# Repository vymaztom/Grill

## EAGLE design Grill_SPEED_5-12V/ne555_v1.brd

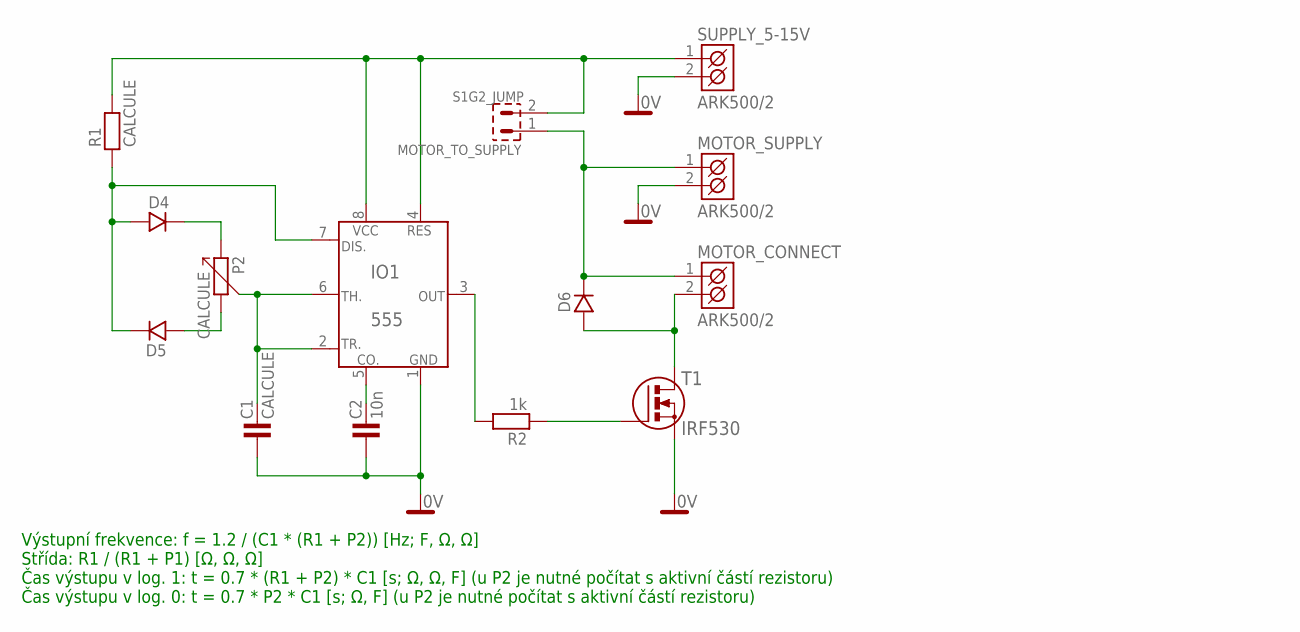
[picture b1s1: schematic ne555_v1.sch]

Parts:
C1: CALCULE; C-7,5
C2: 10n; C-7,5
D4, D5, D6: D_7,5; DO35
IO1: 555; DIL8
MOTOR_CONNECT: ARK500/2
MOTOR_SUPPLY: ARK500/2
MOTOR_TO_SUPPLY: S1G2_JUMP; S1G2_JUM
P2: CALCULE; PC16ML
R1: CALCULE; R-7,5
R2: 1k; R-7,5
SUPPLY_5-15V: ARK500/2
T1: IRF530; TO-220S

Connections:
0V: C1.1, C2.1, IO1.1 (GND), MOTOR_SUPPLY.2 (K2), SUPPLY_5-15V.2 (K2), T1.3 (S)
unnamed: D5.A, P2.2
unnamed: D4.K, P2.1
unnamed: D6.K, MOTOR_CONNECT.1 (K1), MOTOR_SUPPLY.1 (K1), MOTOR_TO_SUPPLY.1
unnamed: D6.A, MOTOR_CONNECT.2 (K2), T1.2 (D)
unnamed: R2.1, T1.1 (G)
unnamed: IO1.3 (OUT), R2.2
unnamed: C2.2, IO1.5 (CO.)
unnamed: D4.A, D5.K, IO1.7 (DIS.), R1.1
unnamed: C1.2, IO1.2 (TR.), IO1.6 (TH.), P2.3
unnamed: IO1.4 (RES), IO1.8 (VCC), MOTOR_TO_SUPPLY.2, R1.2, SUPPLY_5-15V.1 (K1)

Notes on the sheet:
Výstupní frekvence: f = 1.2 / (C1 * (R1 + P2)) [Hz; F, Ω, Ω] Střída: R1 / (R1 + P1) [Ω, Ω, Ω] Čas výstupu v log. 1: t = 0.7 * (R1 + P2) * C1 [s; Ω, Ω, F] (u P2 je nutné počítat s aktivní částí rezistoru) Čas výstupu v log. 0: t = 0.7 * P2 * C1 [s; Ω, F] (u P2 je nutné počítat s aktivní částí rezist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

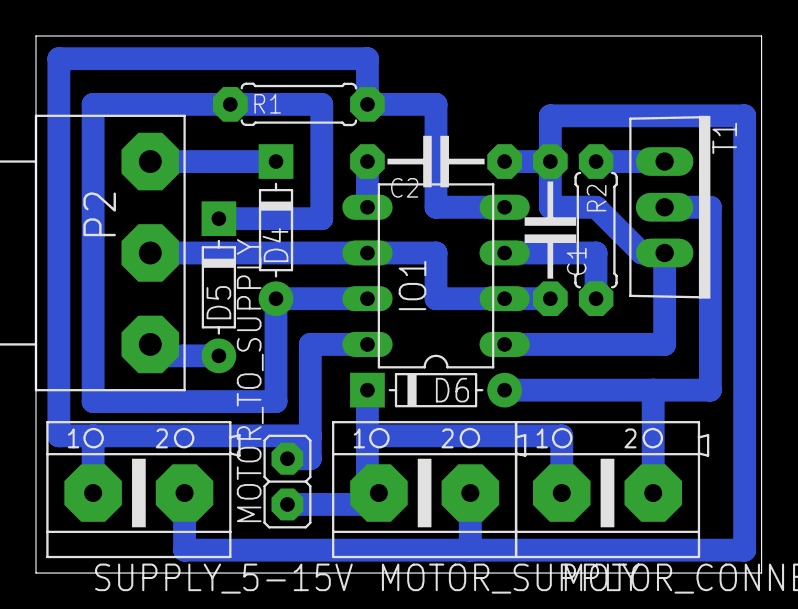
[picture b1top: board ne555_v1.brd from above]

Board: 2 copper layers, 40.3 x 29.8 mm, 14 parts (0 on the bottom side), 11 nets.

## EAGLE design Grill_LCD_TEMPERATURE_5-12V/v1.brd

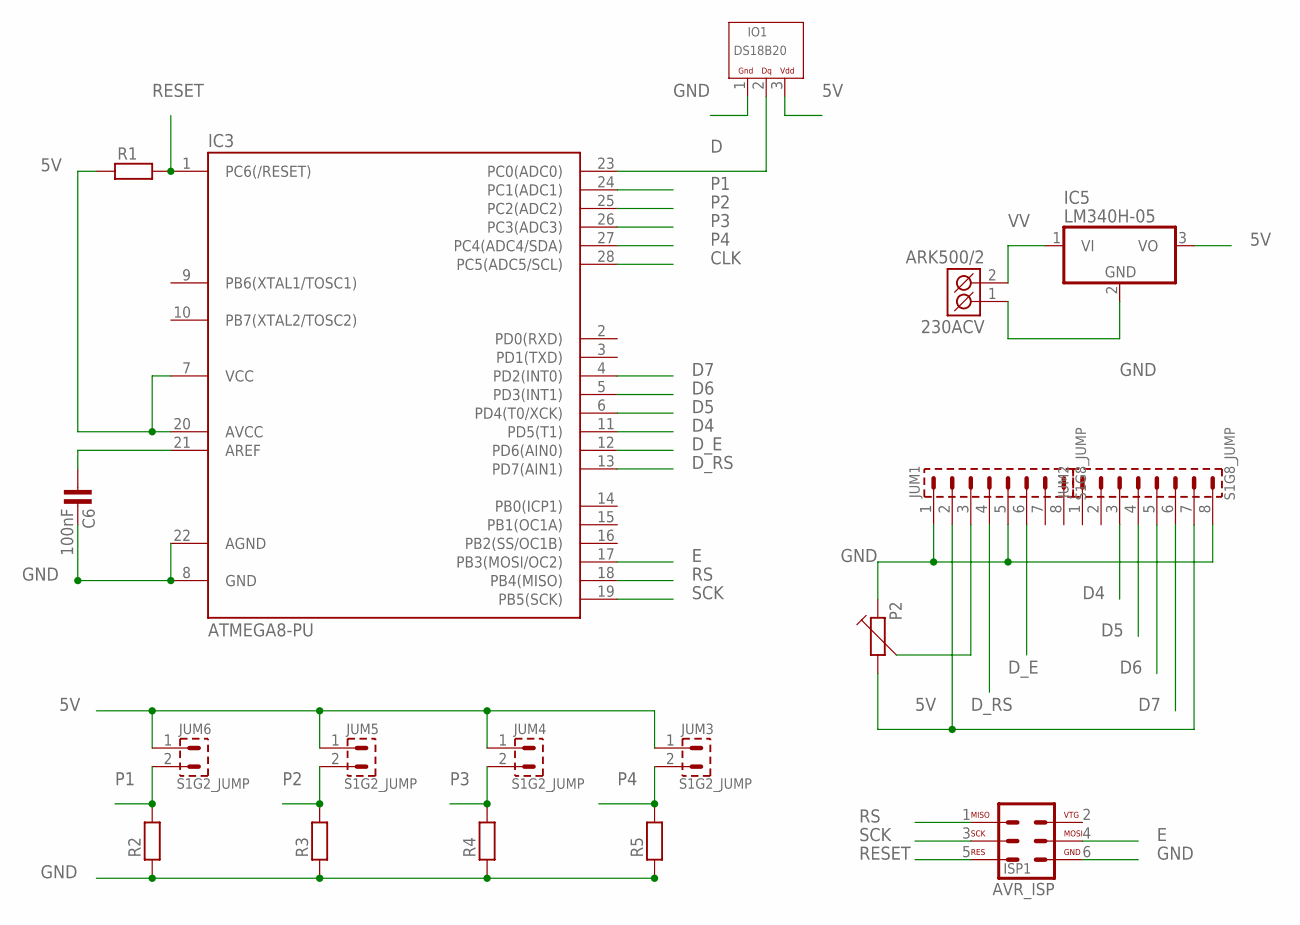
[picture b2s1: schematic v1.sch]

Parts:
230ACV: ARK500/2
C6: 100nF; C-2,5
IC3: ATMEGA8-PU; DIL28-3
IC5: LM340H-05; TO220H
IO1: DS18B20; TO-92
ISP1: AVR_ISP; MLW06G
JUM1, JUM2: S1G8_JUMP; S1G8_JUM
JUM3, JUM4, JUM5, JUM6: S1G2_JUMP; S1G2_JUM
P2: TRIMRPT6V; PT6V
R1, R2, R3, R4, R5: R_7,5; R-7,5

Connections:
5V: IC3.7 (VCC), IC3.20 (AVCC), IC5.3 (VO), IO1.3 (+VCC), JUM1.2, JUM2.7, JUM3.1, JUM4.1, JUM5.1, JUM6.1, P2.2, R1.1
CLK: IC3.28 (PC5(ADC5/SCL))
D: IC3.23 (PC0(ADC0)), IO1.2 (1WIRE)
D4: IC3.11 (PD5(T1)), JUM2.3
D5: IC3.6 (PD4(T0/XCK)), JUM2.4
D6: IC3.5 (PD3(INT1)), JUM2.5
D7: IC3.4 (PD2(INT0)), JUM2.6
D_E: IC3.12 (PD6(AIN0)), JUM1.6
D_RS: IC3.13 (PD7(AIN1)), JUM1.4
E: IC3.17 (PB3(MOSI/OC2)), ISP1.4
GND: 230ACV.1 (K1), C6.2, IC3.8 (GND), IC3.22 (AGND), IC5.2 (GND), IO1.1 (GND), ISP1.6, JUM1.1, JUM1.5, JUM2.8, P2.1, R2.1, R3.1, R4.1, R5.1
unnamed: C6.1, IC3.21 (AREF)
unnamed: JUM1.3, P2.3
P1: IC3.24 (PC1(ADC1)), JUM6.2, R2.2
P2: IC3.25 (PC2(ADC2)), JUM5.2, R3.2
P3: IC3.26 (PC3(ADC3)), JUM4.2, R4.2
P4: IC3.27 (PC4(ADC4/SDA)), JUM3.2, R5.2
RESET: IC3.1 (PC6(/RESET)), ISP1.5, R1.2
RS: IC3.18 (PB4(MISO)), ISP1.1
SCK: IC3.19 (PB5(SCK)), ISP1.3
VV: 230ACV.2 (K2), IC5.1 (VI)

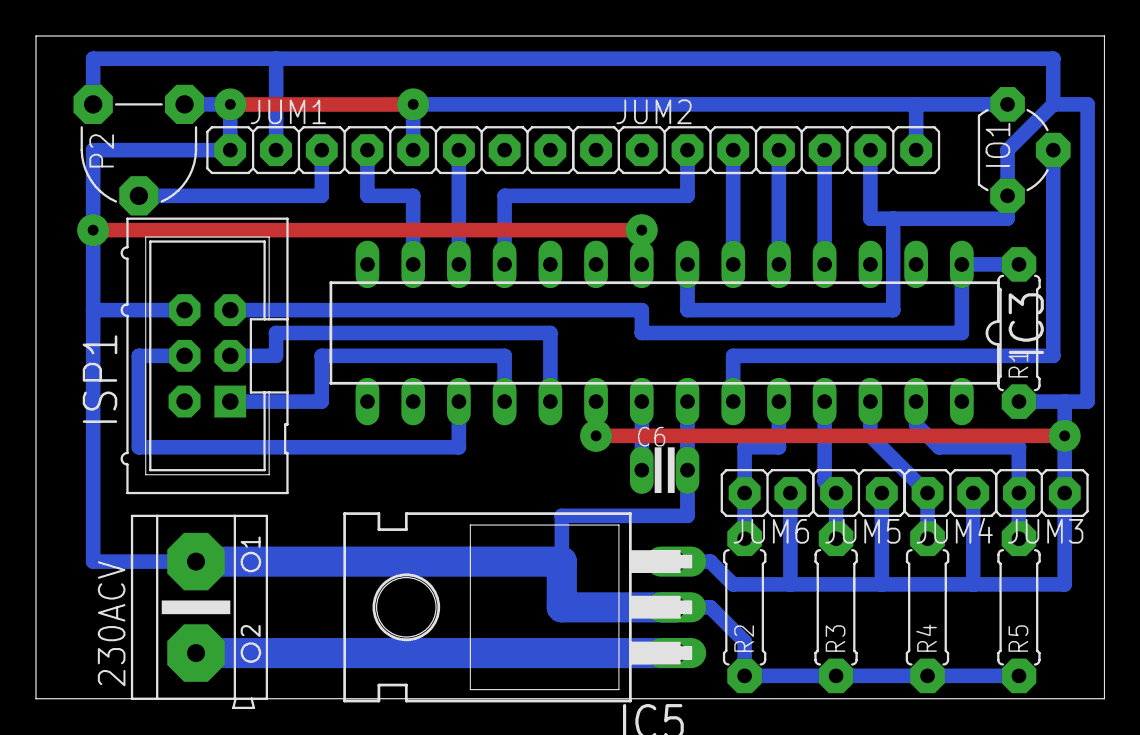
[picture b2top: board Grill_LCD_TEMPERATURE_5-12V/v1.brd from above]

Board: 2 copper layers, 59.4 x 36.8 mm, 18 parts (0 on the bottom side), 20 nets.

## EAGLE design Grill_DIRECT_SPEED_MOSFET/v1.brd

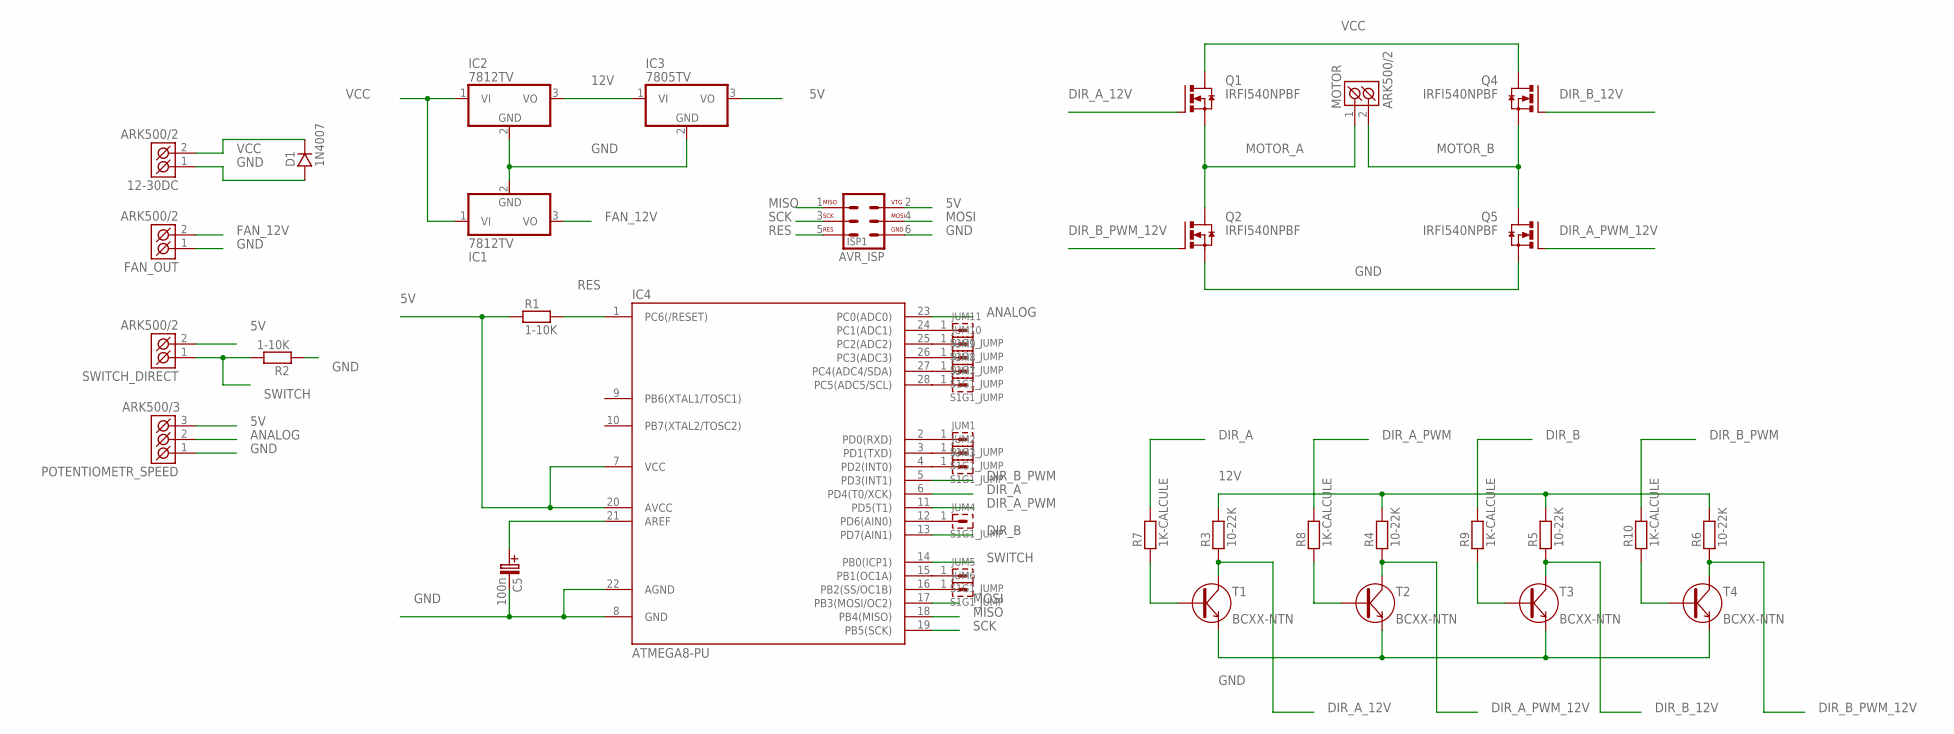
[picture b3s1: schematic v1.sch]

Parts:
12-30DC: ARK500/2
C5: 100n; C-EL_2,5
D1: 1N4007; DO41
FAN_OUT: ARK500/2
IC1, IC2: 7812TV; TO220V
IC3: 7805TV; TO220V
IC4: ATMEGA8-PU; DIL28-3
ISP1: AVR_ISP; MLW06G
JUM1, JUM2, JUM3, JUM4, JUM5, JUM6, JUM7, JUM8, JUM9, JUM10, JUM11: S1G1_JUMP; S1G1_JUM
MOTOR: ARK500/2
POTENTIOMETR_SPEED: ARK500/3
Q1, Q2, Q4, Q5: IRFI540NPBF; TO220BH
R1, R2: 1-10K; R-7,5
R3, R4, R5, R6: 10-22K; R-7,5
R7, R8, R9, R10: 1K-CALCULE; R-7,5
SWITCH_DIRECT: ARK500/2
T1, T2, T3, T4: BCXX-NTN; TO-92

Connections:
5V: IC3.3 (VO), IC4.7 (VCC), IC4.20 (AVCC), ISP1.2, POTENTIOMETR_SPEED.3 (K3), R1.1, SWITCH_DIRECT.2 (K2)
12V: IC2.3 (VO), IC3.1 (VI), R3.2, R4.2, R5.2, R6.2
ANALOG: IC4.23 (PC0(ADC0)), POTENTIOMETR_SPEED.2 (K2)
DIR_A: IC4.6 (PD4(T0/XCK)), R7.2
DIR_A_12V: Q1.G, R3.1, T1.1 (C)
DIR_A_PWM: IC4.11 (PD5(T1)), R8.2
DIR_A_PWM_12V: Q5.G, R4.1, T2.1 (C)
DIR_B: IC4.13 (PD7(AIN1)), R9.2
DIR_B_12V: Q4.G, R5.1, T3.1 (C)
DIR_B_PWM: IC4.5 (PD3(INT1)), R10.2
DIR_B_PWM_12V: Q2.G, R6.1, T4.1 (C)
FAN_12V: FAN_OUT.2 (K2), IC1.3 (VO)
GND: 12-30DC.1 (K1), C5.C- (C_EL-), D1.A, FAN_OUT.1 (K1), IC1.2 (GND), IC2.2 (GND), IC3.2 (GND), IC4.8 (GND), IC4.22 (AGND), ISP1.6, POTENTIOMETR_SPEED.1 (K1), Q2.S, Q5.S, R2.1, T1.3 (E), T2.3 (E), T3.3 (E), T4.3 (E)
MISO: IC4.18 (PB4(MISO)), ISP1.1
MOSI: IC4.17 (PB3(MOSI/OC2)), ISP1.4
MOTOR_A: MOTOR.1 (K1), Q1.S, Q2.D
MOTOR_B: MOTOR.2 (K2), Q4.S, Q5.D
unnamed: IC4.2 (PD0(RXD)), JUM1.1
unnamed: IC4.3 (PD1(TXD)), JUM2.1
unnamed: IC4.4 (PD2(INT0)), JUM3.1
unnamed: IC4.12 (PD6(AIN0)), JUM4.1
unnamed: C5.C+ (C_EL+), IC4.21 (AREF)
unnamed: R7.1, T1.2 (B)
unnamed: IC4.15 (PB1(OC1A)), JUM5.1
unnamed: IC4.16 (PB2(SS/OC1B)), JUM6.1
unnamed: R8.1, T2.2 (B)
unnamed: R9.1, T3.2 (B)
unnamed: R10.1, T4.2 (B)
unnamed: IC4.28 (PC5(ADC5/SCL)), JUM7.1
unnamed: IC4.27 (PC4(ADC4/SDA)), JUM8.1
unnamed: IC4.26 (PC3(ADC3)), JUM9.1
unnamed: IC4.25 (PC2(ADC2)), JUM10.1
unnamed: IC4.24 (PC1(ADC1)), JUM11.1
RES: IC4.1 (PC6(/RESET)), ISP1.5, R1.2
SCK: IC4.19 (PB5(SCK)), ISP1.3
SWITCH: IC4.14 (PB0(ICP1)), R2.2, SWITCH_DIRECT.1 (K1)
VCC: 12-30DC.2 (K2), D1.K, IC1.1 (VI), IC2.1 (VI), Q1.D, Q4.D

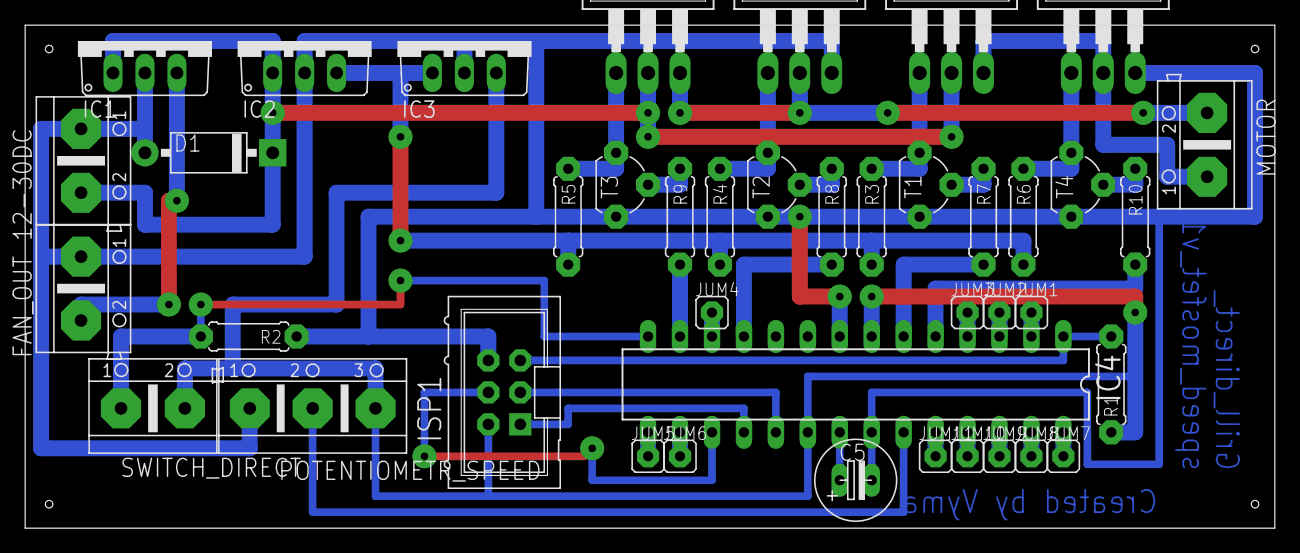
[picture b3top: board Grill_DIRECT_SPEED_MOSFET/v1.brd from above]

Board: 2 copper layers, 99.4 x 40.0 mm, 41 parts (0 on the bottom side), 37 nets.

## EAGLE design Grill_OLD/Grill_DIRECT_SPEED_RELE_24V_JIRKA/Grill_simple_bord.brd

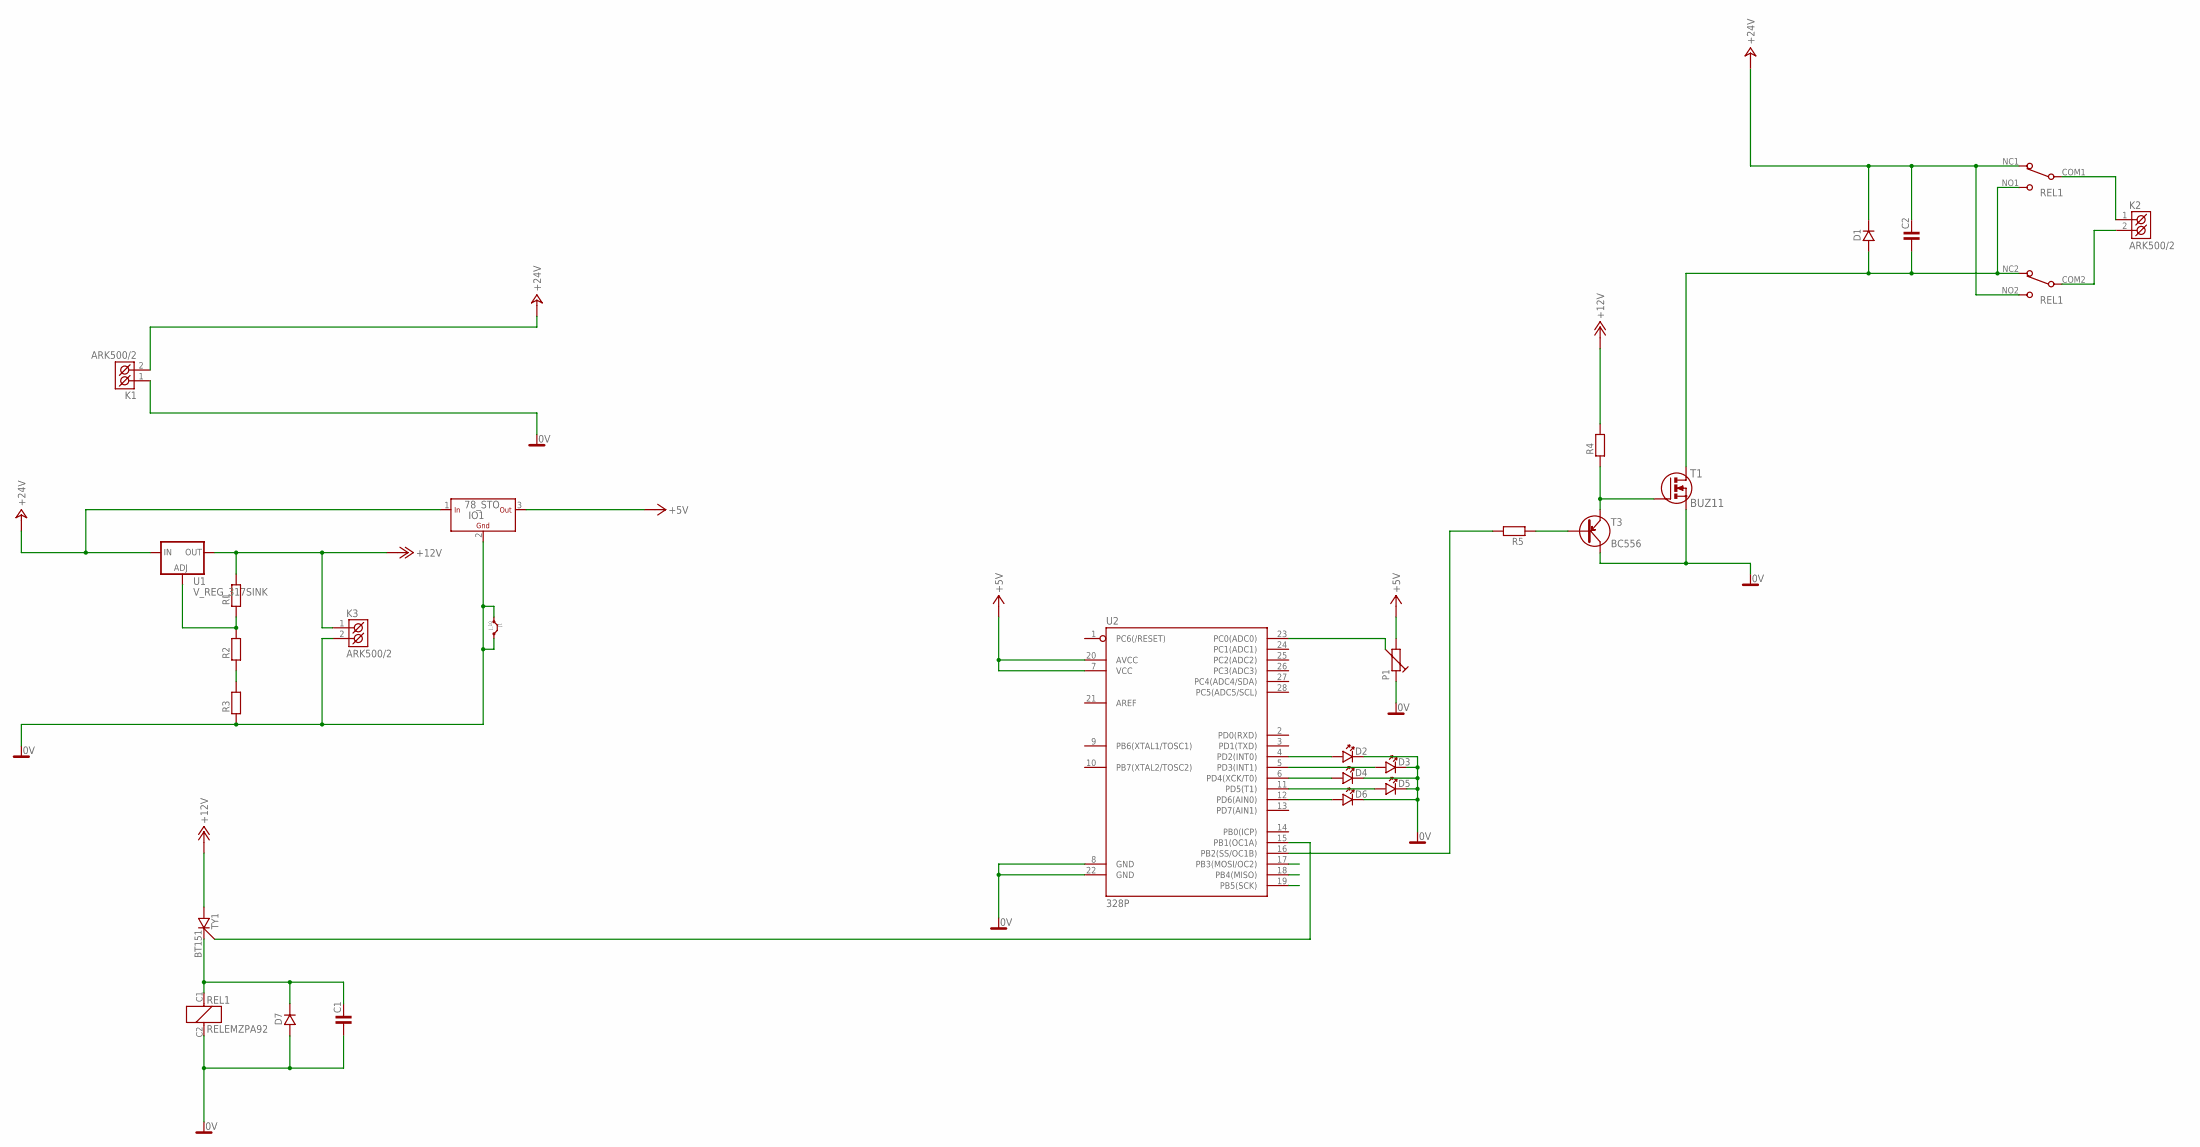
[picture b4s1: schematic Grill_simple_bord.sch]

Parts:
C1, C2: C-KER_5; C-5
D1, D7: D_10; DO41
D2, D3, D4, D5, D6: LED_5
IO1: 78_STO; TO-220S
J1: J_10
K1, K2, K3: ARK500/2
P1: TRIMRPT6V; PT6V
R1, R2, R3, R4, R5: R_7,5; R-7,5
REL1: RELEMZPA92
T1: BUZ11; TO-220S
T3: BC556; TO-92
TY1: BT151; TO-220S
U1: V_REG_317SINK; TO220-ADJ
U2: 328P; DIP28

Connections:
0V: C1.1, D2.K, D3.K, D4.K, D5.K, D6.K, D7.A, IO1.2 (GND), J1.P$1 (1), J1.P$2 (2), K1.1 (K1), K3.2 (K2), P1.1, R3.1, REL1.C2, T1.3 (S), T3.1 (C), U2.8 (GND), U2.22 (GND)
+5V: IO1.3 (OUT), P1.2, U2.7 (VCC), U2.20 (AVCC)
+12V: K3.1 (K1), R1.2, R4.2, TY1.2 (A), U1.OUT
+24V: C2.2, D1.K, IO1.1 (IN), K1.2 (K2), REL1.NC1 (NC), REL1.NO2 (NO), U1.IN
unnamed: K2.2 (K2), REL1.COM2 (COM)
unnamed: R1.1, R2.2, U1.ADJ
unnamed: R2.1, R3.2
unnamed: K2.1 (K1), REL1.COM1 (COM)
unnamed: TY1.3 (G), U2.15 (PB1(OC1A))
unnamed: D2.A, U2.4 (PD2(INT0))
unnamed: C1.2, D7.K, REL1.C1, TY1.1 (K)
unnamed: D3.A, U2.5 (PD3(INT1))
unnamed: R5.1, T3.2 (B)
unnamed: R4.1, T1.1 (G), T3.3 (E)
unnamed: C2.1, D1.A, REL1.NC2 (NC), REL1.NO1 (NO), T1.2 (D)
unnamed: R5.2, U2.16 (PB2(SS/OC1B))
unnamed: P1.3, U2.23 (PC0(ADC0))
unnamed: D4.A, U2.6 (PD4(XCK/T0))
unnamed: D5.A, U2.11 (PD5(T1))
unnamed: D6.A, U2.12 (PD6(AIN0))

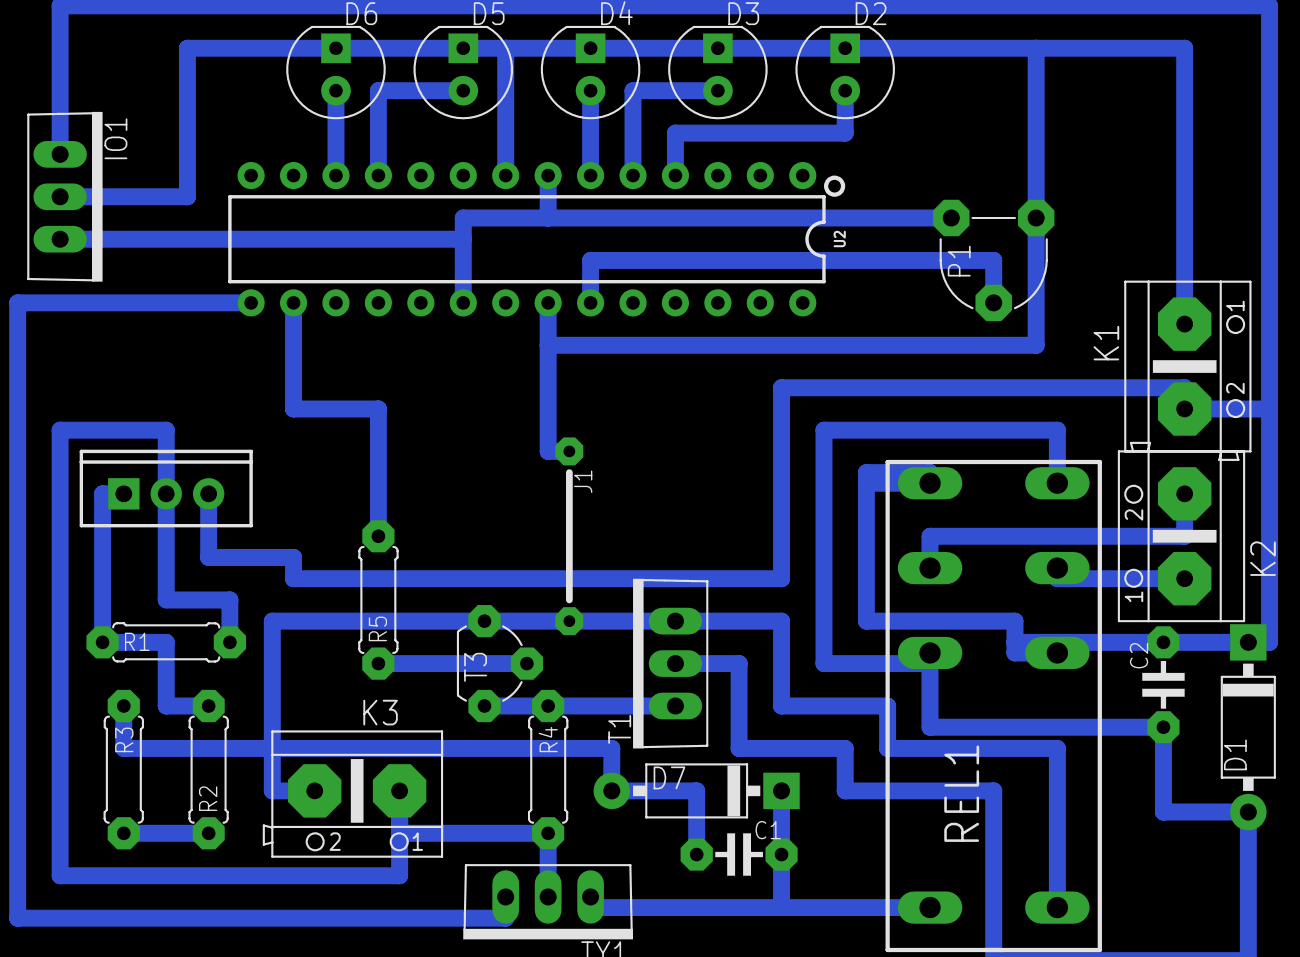
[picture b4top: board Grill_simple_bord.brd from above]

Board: 2 copper layers, 26 parts (0 on the bottom side), 20 nets.

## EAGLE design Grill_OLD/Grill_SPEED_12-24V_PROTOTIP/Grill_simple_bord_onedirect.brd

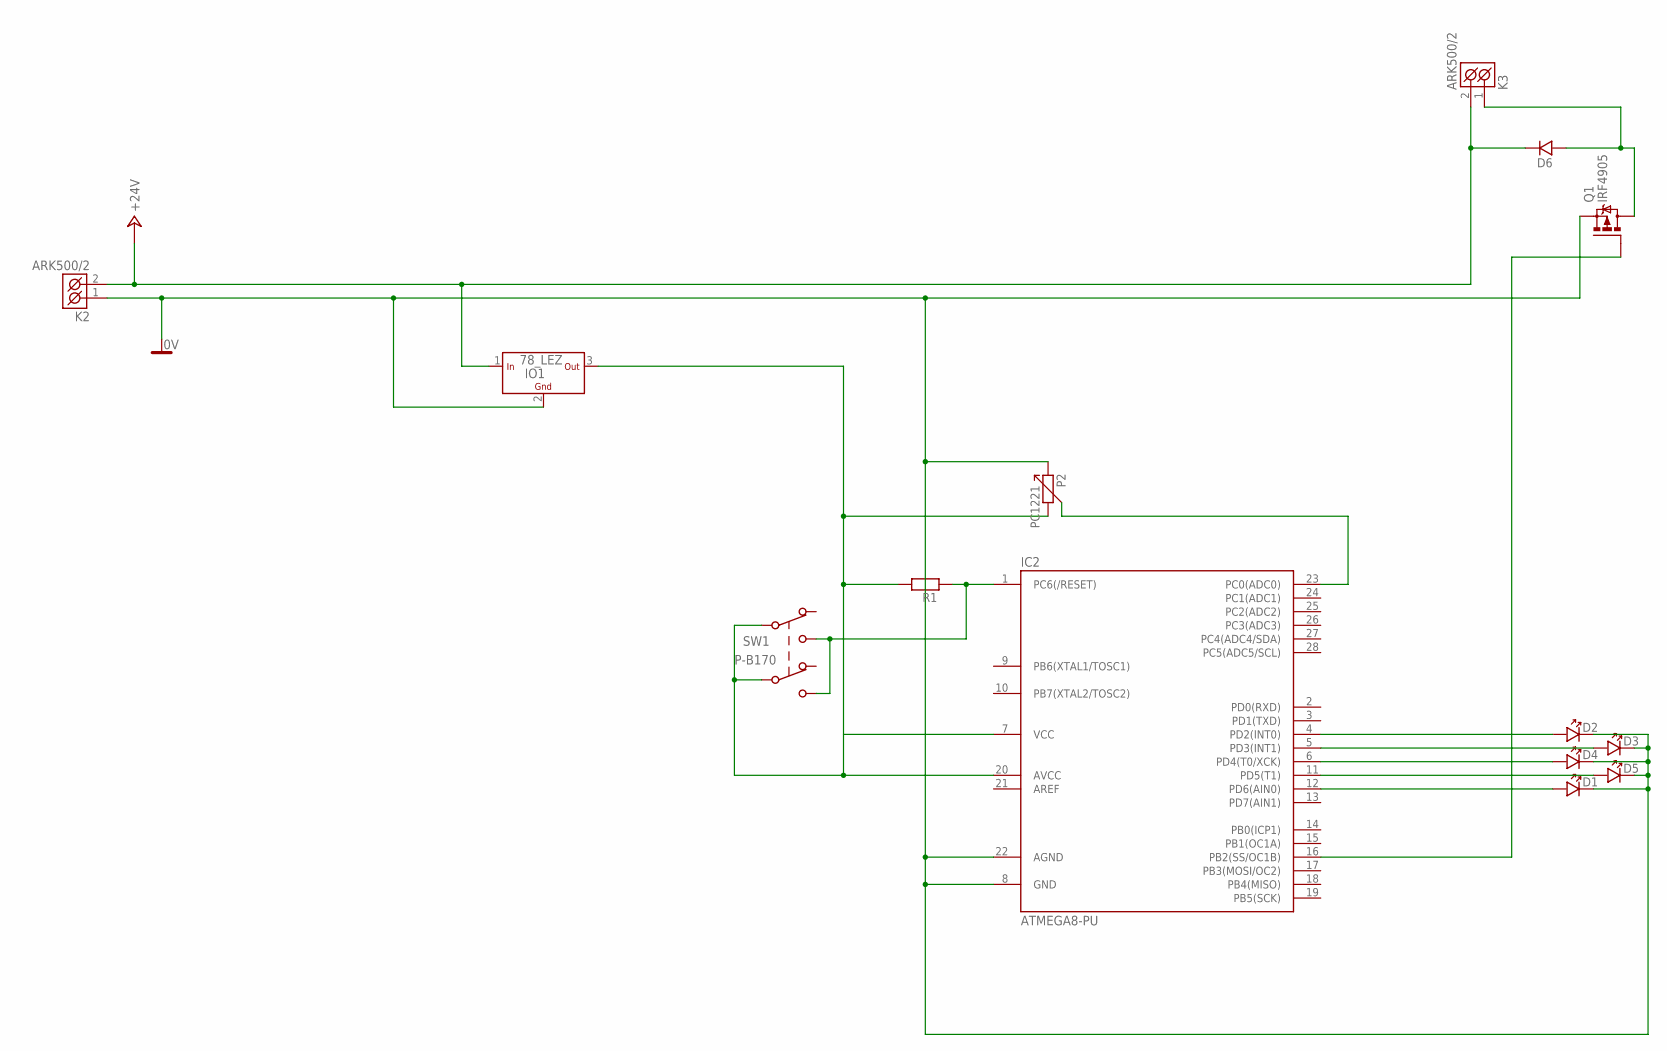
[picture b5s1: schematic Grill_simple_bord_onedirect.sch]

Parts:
D1, D2, D3, D4, D5: LED_5
D6: D_10; DO41
IC2: ATMEGA8-PU; DIL28-3
IO1: 78_LEZ; TO-220
K2, K3: ARK500/2
P2: PC1221
Q1: IRF4905; TO220BH
R1: R_7,5; R-7,5
SW1: P-B170

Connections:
0V: D1.K, D2.K, D3.K, D4.K, D5.K, IC2.8 (GND), IC2.22 (AGND), IO1.2 (GND), K2.1 (K1), P2.1, Q1.S
+24V: D6.K, IO1.1 (IN), K2.2 (K2), K3.2 (K2)
unnamed: D5.A, IC2.11 (PD5(T1))
unnamed: D6.A, K3.1 (K1), Q1.D
unnamed: IC2.16 (PB2(SS/OC1B)), Q1.G
unnamed: IC2.23 (PC0(ADC0)), P2.3
unnamed: D2.A, IC2.4 (PD2(INT0))
unnamed: D3.A, IC2.5 (PD3(INT1))
unnamed: D4.A, IC2.6 (PD4(T0/XCK))
unnamed: D1.A, IC2.12 (PD6(AIN0))
unnamed: IC2.1 (PC6(/RESET)), R1.1, SW1.2 (R1), SW1.5 (R2)
unnamed: IC2.7 (VCC), IC2.20 (AVCC), IO1.3 (OUT), P2.2, R1.2, SW1.3 (X1), SW1.6 (X2)

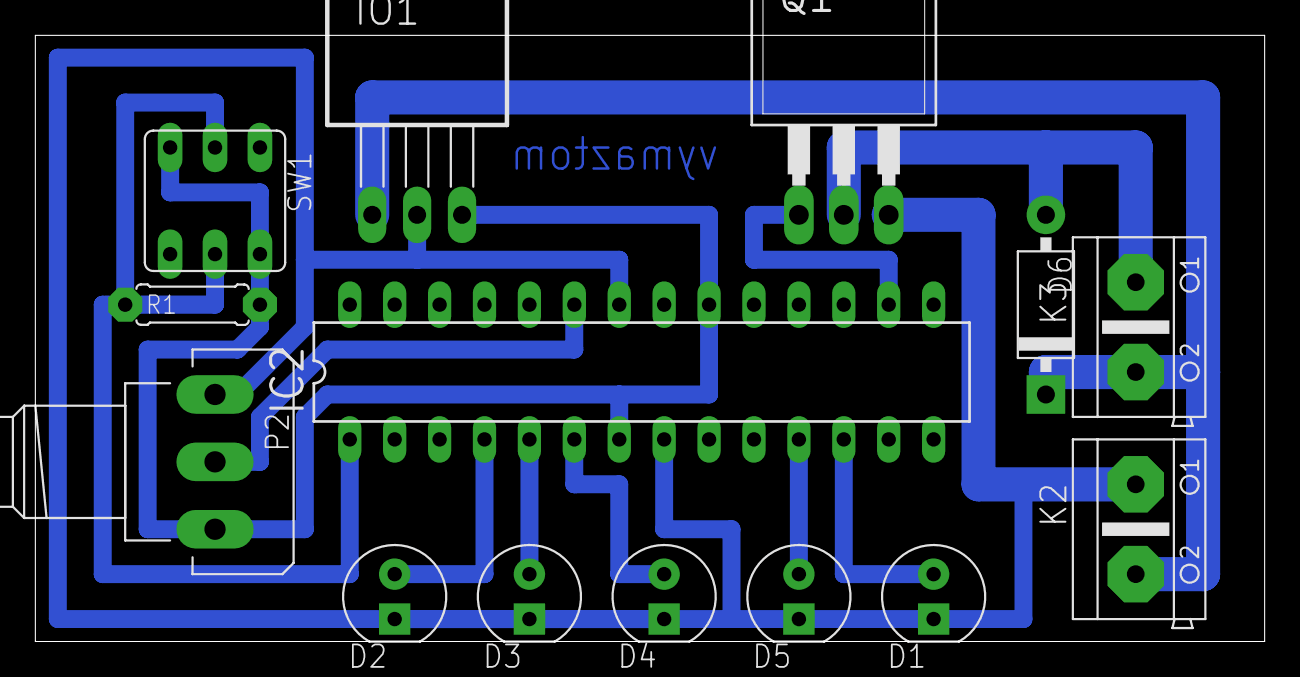
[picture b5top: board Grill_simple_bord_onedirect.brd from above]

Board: 2 copper layers, 69.5 x 34.3 mm, 14 parts (0 on the bottom side), 12 nets.

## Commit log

2018-10-09 Start of Projets
2018-10-16 Update LICENSE

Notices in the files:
parts and their libraries:
Copyright (C) PaJa 2011-2014
Copyright (C) PaJa 2001-2014
SparkFun-IC-Power: Licensing: Creative Commons ShareAlike 4.0 International - https://creativecommons.org/licenses/by-sa/4.0
